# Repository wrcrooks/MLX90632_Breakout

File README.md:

# MLX90632 Breakout
A minimal, castellated breakout board for the MLX90632 chip

Designed for [Build A CubeSAT](https://www.youtube.com/@buildacubesat)

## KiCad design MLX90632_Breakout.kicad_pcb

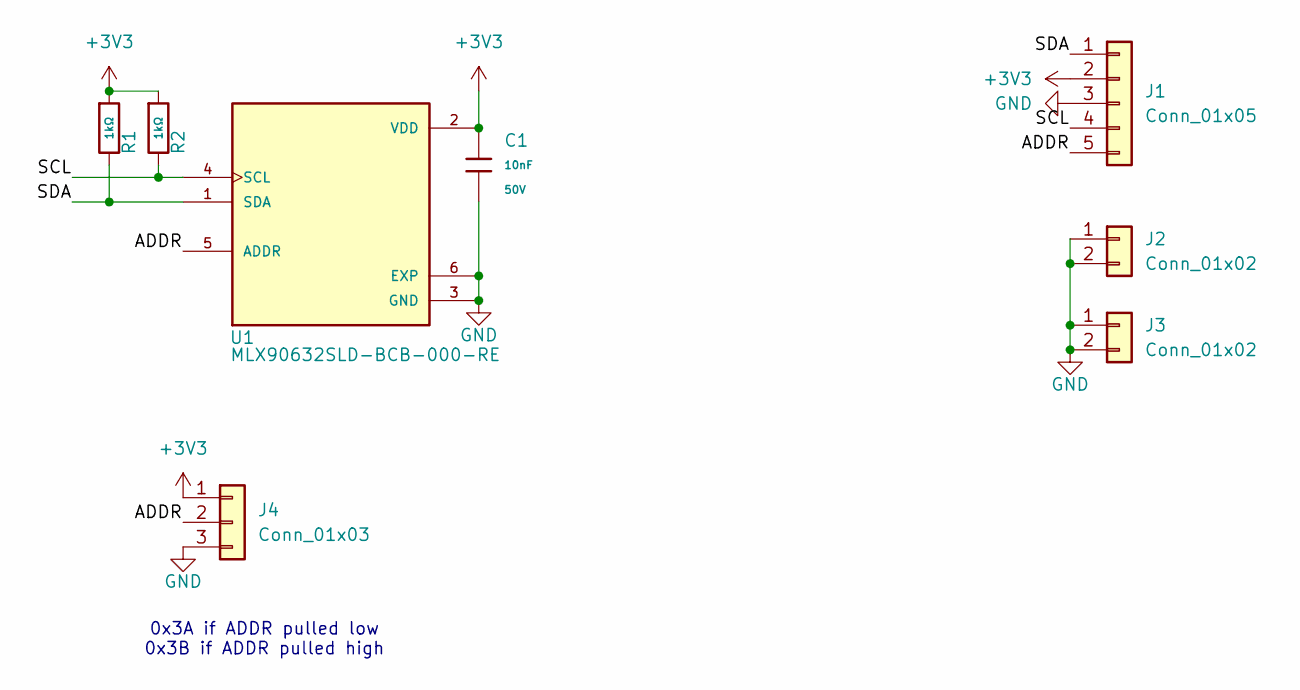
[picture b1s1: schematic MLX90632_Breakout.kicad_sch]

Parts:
C1: 10nF; C_0402; Voltage Rated 50V; Tolerance ±10%; Part CL05B103KB5NNNC; LCSC C15195
J1: Conn_01x05; PinHeader_1x05_P2.00mm_Vertical
J2, J3: Conn_01x02; PinHeader_1x02_P2.00mm_Vertical
J4: Conn_01x03; SolderJumper-3_P1.3mm_Open_Pad1.0x1.5mm_NumberLabels
R1, R2: 1kΩ; R_0402; Overload Voltage (Max) 50V; Tolerance ±1%; Part 0402WGF1001TCE; LCSC C11702
U1: MLX90632SLD-BCB-000-RE; IC_MLX90632SLD-BCB-000-RE; PARTREV 12

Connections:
+3V3: C1.1, J1.2, J4.1, R1.1, R2.1, U1.2 (VDD)
/ADDR: J1.5, J4.2, U1.5 (ADDR)
/SCL: J1.4, R2.2, U1.4 (SCL)
/SDA: J1.1, R1.2, U1.1 (SDA)
GND: C1.2, J1.3, J2.1, J2.2, J3.1, J3.2, J4.3, U1.3 (GND), U1.6 (EXP)

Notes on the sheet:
0x3A if ADDR pulled low 0x3B if ADDR pulled high

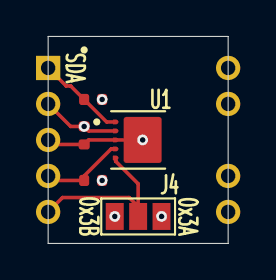
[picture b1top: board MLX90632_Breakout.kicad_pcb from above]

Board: 2 copper layers, 10.0 x 11.5 mm, 8 parts (0 on the bottom side), 5 nets.

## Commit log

2025-07-23 Finalized Design
2025-07-23 Added README
2025-07-23 Added Gerber Files
2025-07-23 Excluded J4 from BOM and CPL
2025-07-23 Excluded all Edge Connectors from BOM and CPL
2025-07-23 Added library components for MLX90632
